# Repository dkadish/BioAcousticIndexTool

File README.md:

# BioAcoustic Index Tool (BAIT)

A smart, field-deployable sensor that automatically calculates acoustic indices and captures environmental data in real time.

BAIT records soundscape data and computes standard ecoacoustic metrics — including the **Acoustic Complexity Index (ACI)**, **Acoustic Diversity Index (ADI)**, and **Acoustic Difference Index (ADE)** — directly on-device. Environmental readings (temperature, humidity, light, and battery level) are logged alongside the acoustic data to SD card, with optional LoRaWAN transmission.

## Table of Contents

- [Project Overview](#project-overview)
- [Repository Structure](#repository-structure)
- [Hardware Versions](#hardware-versions)
- [Getting Started](#getting-started)
- [Contributing](#contributing)
- [License](#license)

## Project Overview

Traditional soundscape monitoring requires transporting recording equipment to the field, recording raw audio files, and then processing them offline. BAIT eliminates the offline processing step by computing acoustic indices on the microcontroller itself. This reduces storage requirements and allows near-real-time data delivery over low-power wide-area networks (LoRaWAN).

### Acoustic Indices Computed

| Index | Description |
|-------|-------------|
| **ACI** | Acoustic Complexity Index — captures the variability in sound intensity across frequency bins |
| **ADI** | Acoustic Diversity Index — measures the diversity of sound across frequency bands (Shannon entropy) |
| **ADE** | Acoustic Difference Index — measures the difference between consecutive time windows |
| **BI** | Bioacoustic Index — area of the mean spectrum above its minimum between 2 and 8 kHz |
| **H** | Total acoustic entropy — product of temporal (Ht) and spectral (Hf) entropy |
| **Events** | Acoustic event count — rises of the sound level above the background noise |

## Repository Structure

```
BioAcousticIndexTool/
├── firmware/
│   ├── bait/          # v1 firmware (Teensy 3.5 / 3.6 / MicroMod)
│   └── bait2/         # v2 firmware (Teensy MicroMod — active development)
├── electronics/
│   ├── BAIT.fzz       # v1 Fritzing schematic
│   └── BAIT2_MicroMod/ # v2 Eagle PCB & schematic
├── enclosure/
│   ├── BAIT.dwg       # AutoCAD drawing
│   └── BAIT.f3z       # Fusion 360 design
├── analysis/          # R & Python analysis notebooks
├── data/              # Sample raw and processed data
└── docs/              # Developer documentation
```

## Hardware Versions

### BAIT v1
- **Processor:** Teensy 3.5 or 3.6
- **PCB:** Custom carrier board designed in Fritzing
- **Sensors:** Si7021 (temperature/humidity), TSL2561 (light), battery voltage divider
- **Storage:** SD card via SdFat
- **Power:** Low-power sleep via Snooze library

### BAIT v2 (Active)
- **Processor:** Teensy MicroMod on SparkFun MicroMod carrier
- **PCB:** Custom Eagle carrier board ([`electronics/BAIT2_MicroMod`](electronics/BAIT2_MicroMod))
- **Sensors:** BME680 (temperature, humidity, pressure, gas), TSL2591 (light), BQ27441 LiPo fuel gauge
- **Communication:** LoRaWAN via Seeed WIO-E5 (The Things Network)
- **Storage:** SD card

## Getting Started

### Prerequisites

- [PlatformIO](https://platformio.org/) — used for building and uploading firmware
- [CLion](https://www.jetbrains.com/clion/) (recommended IDE) or VS Code with PlatformIO extension
- A Teensy MicroMod board (for BAIT v2) or Teensy 3.5/3.6 (for BAIT v1)

See [`docs/developing.md`](docs/developing.md) for detailed setup instructions.

### Building the Firmware

1. Clone this repository (including submodules):
   ```bash
   git clone --recurse-submodules https://github.com/dkadish/BioAcousticIndexTool.git
   ```

2. Open the relevant firmware directory in your IDE:
   - BAIT v2: `firmware/bait2/`
   - BAIT v1: `firmware/bait/`

3. Build and upload using PlatformIO:
   ```bash
   # For BAIT v2
   cd firmware/bait2
   pio run -e teensymm -t upload
   ```

   See each firmware directory's README for full build instructions.

### Data Analysis

The [`analysis/`](analysis/) directory contains Jupyter notebooks and R Markdown files for verifying acoustic index calculations and visualising results. See [`analysis/README.md`](analysis/README.md) for details.

## Contributing

Contributions are welcome! Please read [`docs/developing.md`](docs/developing.md) for information on setting up your development environment.

## License

This project is licensed under the terms in the [LICENSE](LICENSE) file.

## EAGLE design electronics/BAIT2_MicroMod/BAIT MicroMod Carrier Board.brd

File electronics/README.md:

# Electronics

Hardware design files for the BioAcoustic Index Tool (BAIT) custom carrier boards.

## Contents

| File / Directory | Description |
|-----------------|-------------|
| `BAIT.fzz` | BAIT v1 schematic and PCB layout (Fritzing) |
| `BAIT_bb.png` | BAIT v1 breadboard wiring diagram |
| `BAIT2_MicroMod/` | BAIT v2 custom carrier board for Teensy MicroMod (Eagle) |

## BAIT v1

The v1 board is a through-hole prototype carrier designed in [Fritzing](https://fritzing.org/).

**File:** `BAIT.fzz`

Open with the Fritzing application to view the schematic and breadboard layout.

## BAIT v2 — MicroMod Carrier Board (`BAIT2_MicroMod/`)

The v2 carrier board is designed in [Eagle](https://www.autodesk.com/products/eagle/overview) and mounts a **Teensy MicroMod** processor module.

| File | Description |
|------|-------------|
| `BAIT MicroMod Carrier Board.sch` | Eagle schematic |
| `BAIT MicroMod Carrier Board.brd` | Eagle PCB layout |
| `eagle.epf` | Eagle project file |
| `gerbers/` | Gerber files for PCB fabrication |
| `Assembly/` | Assembly documentation and BOM |

### Key Features

- **Processor socket:** SparkFun MicroMod M.2 connector (accepts Teensy MicroMod)
- **Sensors:** BME680 (temperature, humidity, pressure, gas), TSL2591 (light), BQ27441 (LiPo fuel gauge)
- **Communication:** Seeed WIO-E5 LoRaWAN module connector
- **Storage:** MicroSD card slot
- **Power:** LiPo battery connector with charging circuit

### Ordering PCBs

Use the Gerber files in `BAIT2_MicroMod/gerbers/` to order boards from a PCB fabrication service such as OSH Park, JLCPCB, or PCBWay.

## Tools Required

- [Fritzing](https://fritzing.org/) — for opening BAIT v1 design files
- [Autodesk Eagle](https://www.autodesk.com/products/eagle/overview) — for opening BAIT v2 design files

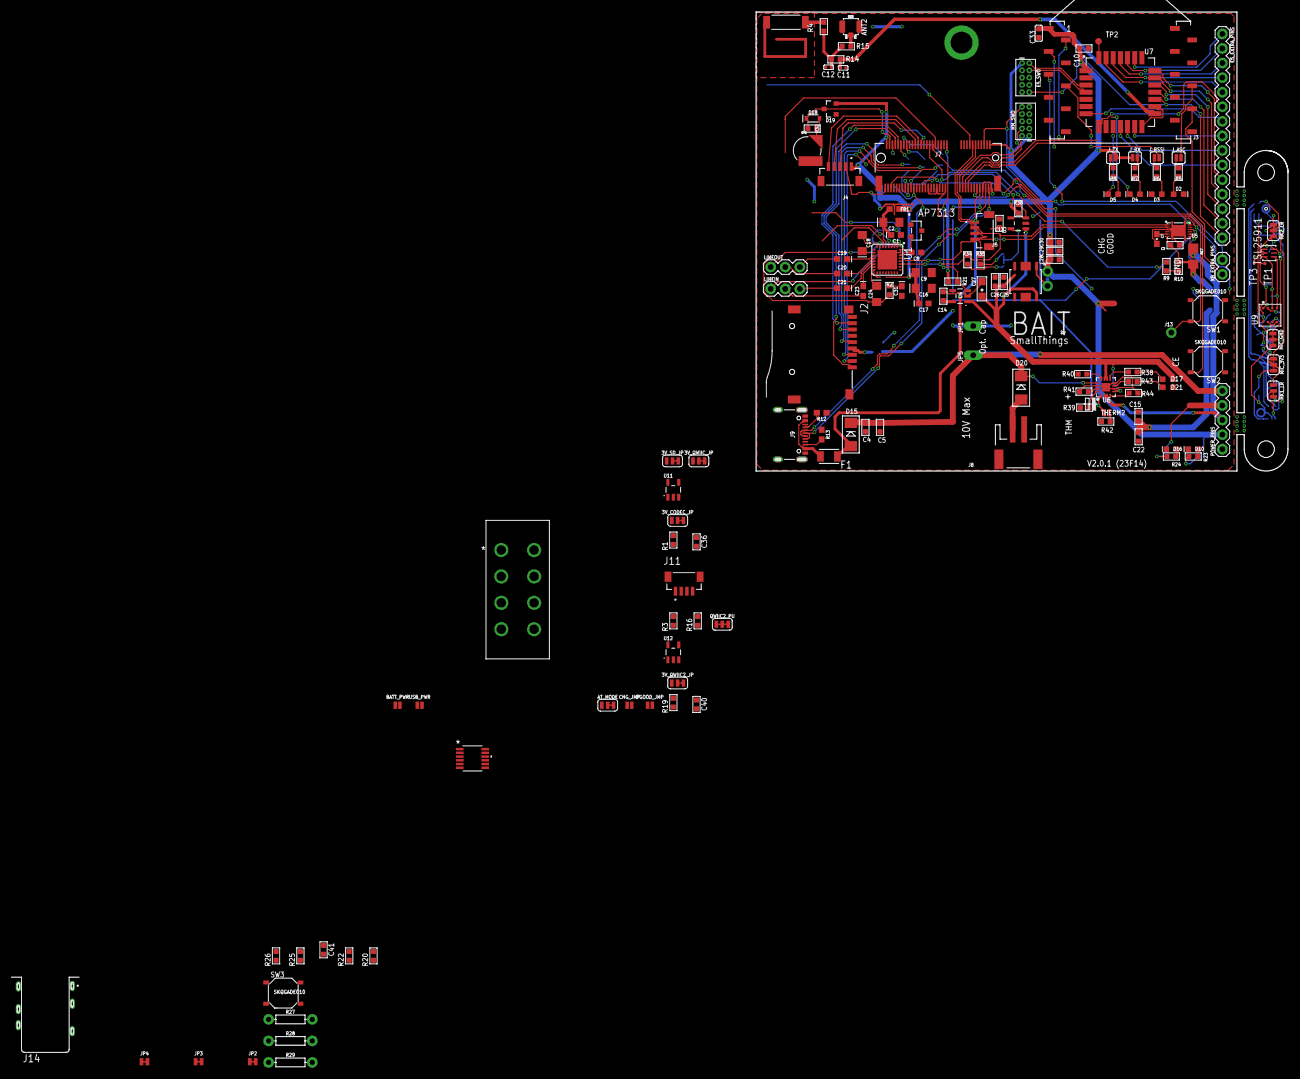
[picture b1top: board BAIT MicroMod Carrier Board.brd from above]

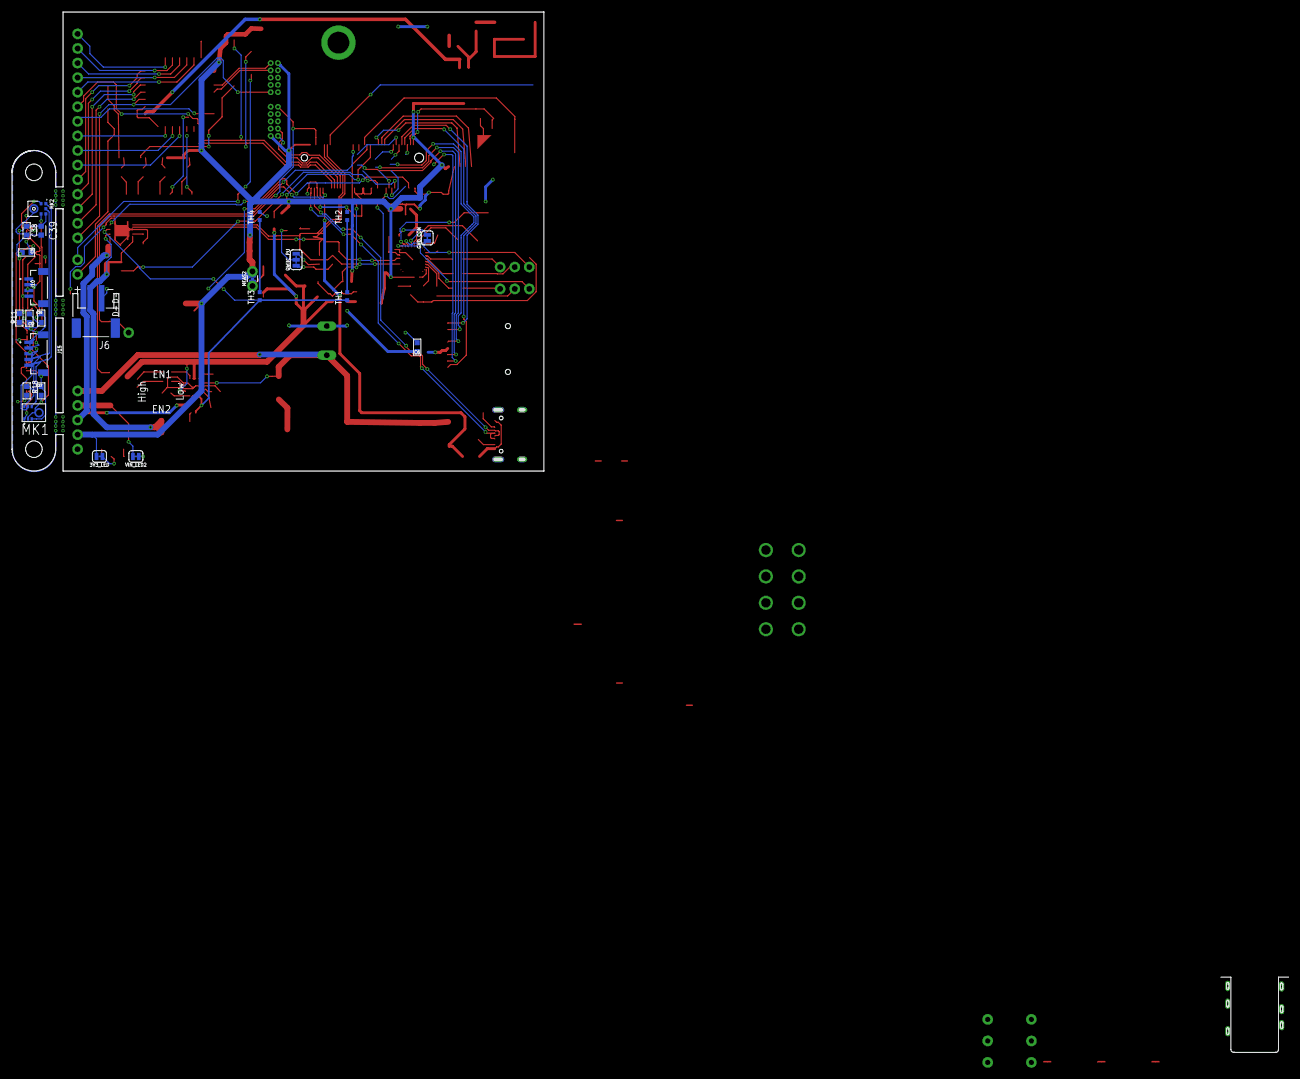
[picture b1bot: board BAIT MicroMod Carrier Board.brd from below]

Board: 2 copper layers, 92.7 x 80.0 mm, 174 parts (23 on the bottom side), 160 nets.

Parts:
3V3_LED: SMT-JUMPER_2_NC_TRACE_SILK
3V_CODEC_JP, 3V_QWIIC2_JP, 3V_QWIIC_JP, 3V_SD_JP: MK2_LR; SMT-JUMPER_3_1-NC_TRACE_SILK
ANT1: 0868AT43A0020EANT_0868AT43A0020E_JOT; ANT_0868AT43A0020E_JOT
ANT2: U-FL Connector; U-FL3P-SMD-2.6X2.6X1.0MM
AT_MODE: MK2_LR; SMT-JUMPER_3_1-NC_TRACE_SILK
BATT_PWR: SMT-JUMPER_2_NO_NO-SILK
BT1: ML414H; ML414H_IV01E
C1, C8, C17, C19, C20, C21, C23, C31: 2.2uF; 0603-POLAR
C2, C9, C16, C24: 0.1uF; EIA3216
C3, C13, C14, C28, C36, C40: 1uf; C0603
C4, C5, C10, C15, C22: 4.7uf; C0603
C6, C26, C29, C32, C34, C35, C37, C38, C41: 100nf; C0603
C7: 0.47uF; 0603-CAP
C11, C12: DNP; C0402
C18: 0.15uF; EIA3216
C25, C30: 220nf; C0603
C27: 10uf; AVX-A
C33: 4.7uF; C0603
C39: 220pF; CAPC1608X85
CHG_JMP: SMT-JUMPER_2_NO_NO-SILK
D2, D3, D4, D21: GREEN; LED-0603
D5, D10, D17: RED; LED-0603
D15, D20: SK34A; SMADIODE
D16: Yellow; LED-0603
D18: 3A/10V/280mV; SOD-323
D19: BAS70-05; SOT23-3
E5_EXTRA_PINS: 1X15
E5_SWO: JTAG; 2X5-PTH-1.27MM
F1: 6V/2A; FUSC3215X82N
FB1: 600Ω/1.8A; 0603
GND_CON: SMT-JUMPER_2_NC_TRACE_SILK
H5: STAND-OFF-REFLOW2.5MM_TALL; STAND-OFF-REFLOW-M2.5
J2: ST-TF-003A; SUNTECH_ST-TF-003A
J3: XBEE-SMD
J4, J15: BM05B-SRSS-TB(LF)(SN); JST_BM05B-SRSS-TB(LF)(SN)
J5, J10, J11: QWIIC_RIGHT_ANGLE; JST_BM04B-SRSS-TB(LF)(SN)
J6: JST 2PH; JST-PH-2-SMT-RA
J7: MICROMOD-2222-C; M.2-CONNECTOR-E
J8: JST-2-SMD
J9: USB-C-16P-2LAYER-PADS
J12: L203011MS02QECONN8_MS02QE_CNK; CONN8_MS02QE_CNK
J13: 1X01_NO_SILK
J14: SJ-3551B-MSMT-TR-67; CUI_SJ-3551B-MSMT-TR-67
JP1, JP5: 1X01_OVAL
JP2, JP3, JP4: JUMPER-SMT_2_NC_TRACE_NO-SILK; SMT-JUMPER_2_NC_TRACE_NO-SILK
J_ASC: JUMPER-SMT_2_NO_SILK; SMT-JUMPER_2_NO_SILK
J_RSSI: JUMPER-SMT_2_NO_SILK; SMT-JUMPER_2_NO_SILK
J_RX: JUMPER-SMT_2_NO_SILK; SMT-JUMPER_2_NO_SILK
J_TX: JUMPER-SMT_2_NO_SILK; SMT-JUMPER_2_NO_SILK
LINEIN: 1X03
LINEOUT: 1X03
MEAS2: COMBO-JUMPER_2_NC_TRACE
MIC_3V3: SMT-JUMPER_3_2-NC_TRACE_SILK
MIC_GND: SMT-JUMPER_3_2-NC_TRACE_SILK
MK1: ICS-43432
MK1_LR: MK1_LR; SMT-JUMPER_3_1-NC_TRACE_SILK
MK2: SPH0645LM4H-B; MIC_SPH0645LM4H-B
MK2_LR: MK2_LR; SMT-JUMPER_3_1-NC_TRACE_SILK
MM_SWO: JTAG; 2X5-PTH-1.27MM
PGOOD_JMP: SMT-JUMPER_2_NO_NO-SILK
POWER_PINS: 1X05
QWIIC2_PU: SMT-JUMPER_3_2-NC_TRACE_SILK
QWIIC_PU: SMT-JUMPER_3_2-NC_TRACE_SILK
R1, R18, R19, R20, R21, R36: 100K; R0603
R2, R3, R16, R34, R35: 2.2K; R0603
R4, R14, R15: 0R; R0603
R5, R11, R24: 4.7K; R0603
R6, R7, R8, R23, R40: 1K 1/10W; R0603
R9, R38, R41, R42, R43, R44: 10K 1/10W; R0603
R10: 20K; R0603
R12, R13: 5.1k; 0603
R17: 0.01; 1206
R22: 1.02M; R0603
R25: 61.9k; R0603
R26: 115k; R0603
R27, R28, R29: AXIAL-0.3
R32: 3.3K; R0603
R39: 590; R0603
SW1, SW2, SW3: SKQGADE010; SW4-SMD-5.2X5.2X1.5MM
TH1, TH2, TH3, TH4: 10k; THERM_NTCG163JX103DT1S
THERM2: SMT-JUMPER_2_NO_NO-SILK
TP1, TP3: PTR1TP06R; TP06R
TP2: TEST; TP-D45MIL
U1: SGTL5000-32; QFN-32-5MM
U2: AP7313; SOT-23_DIO
U3, U4, U11, U12: 3.3V; SOT23-5
U5: BQ27441-G1; PDSO-N12
U6: BQ24074; QFN16_3MM
U7: LoRa-E5-HF; MOUDLE28P-1.25-12X12X2.5MM
U8: S-1172B33-E6T1U; HSOP-6_FH006-A-P-SD-2.1_ABL
U9: BOSCH_TOOLS_BME680BOSCH_TOOLS_BME680_0_0; BOSCH_TOOLS_BME680_0
U10: TSL25911; SON-06-FN_2000X2400_AMS
U13: LTC2956IMS-1PBF; MSOP-12_MS_LIT
USB_PWR: SMT-JUMPER_2_NO_NO-SILK
VIN_LED2: SMT-JUMPER_2_NC_TRACE_SILK
XB_EXTRA_PINS: 1X02

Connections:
1.8V: C7.1, U5.5
3.3V: 3V3_LED.2, 3V_CODEC_JP.1, 3V_QWIIC2_JP.1, 3V_QWIIC_JP.1, 3V_SD_JP.1, AT_MODE.3, C10.2, C28.1, C29.1, C30.1, C33.2, D19.2, E5_SWO.1, J3.1, J4.1, J7.2, J7.74, J_RX.1, J_TX.2, MEAS2.2, MEAS2.4, MM_SWO.1, POWER_PINS.2, R1.2, R19.2, R21.2, R36.2, U7.1
3V3_B: C34.1, C35.1, J10.2, J15.1, MIC_3V3.2, MK1_LR.1, MK2_LR.3, TP1.TP, U9.8, U10.5
3V3_ICS: C37.1, MIC_3V3.3, MK1.3
3V3_SPH: C38.1, C39.1, MIC_3V3.1, MK2.5
3V_CODEC: 3V_CODEC_JP.3, C9.+, C16.+, C17.+, FB1.1, U1.20, U2.1
3V_EN: U8.3, U13.8
3V_QWIIC: 3V_QWIIC_JP.3, J5.2, QWIIC_PU.2
3V_QWIIC2: 3V_QWIIC2_JP.3, J11.2, QWIIC2_PU.2
3V_QWIIC_OUT: 3V_QWIIC_JP.2, C13.1
3V_QWIIC_OUT1: 3V_CODEC_JP.2, C36.1, U11.5
3V_QWIIC_OUT2: 3V_QWIIC2_JP.2, C40.1, U12.5
3V_SD: 3V_SD_JP.3, C6.1, J2.4
3V_SD_OUT: 3V_SD_JP.2, C14.1, U4.5
!BOOT!: J7.11, SW2.2
!CE: R44.1, U6.4
!CHG: R38.1, U6.9
!OFFALERT!: J7.38, U13.10
!ONALERT!: J7.34, U13.12
!PB: SW3.2, U13.7
!PBOUT!: J7.65, U13.9
!PGOOD: R43.1, U6.7
!RESET!: J7.6, J13.1, MM_SWO.10, SW1.2
!SLEEP!: J7.8, U13.11
AGND: C18.-, GND_CON.1, LINEIN.1, LINEOUT.1, U1.1, U1.3, U1.7
ASC: J3.15, J_ASC.2
CODEC_EN: J7.48, R1.1, U11.3
GND: ANT2.GND1, ANT2.GND2, AT_MODE.1, BT1.-, C1.-, C2.-, C3.2, C4.2, C5.2, C6.2, C7.2, C8.-, C9.-, C10.1, C11.1, C12.1, C13.2, C14.2, C15.2, C16.-, C17.-, C22.2, C25.2, C26.2, C27.-, C28.2, C29.2, C30.2, C31.-, C33.1, C36.2, C40.2, C41.2, D2.C, D3.C, D10.C, D16.C, E5_SWO.3, E5_SWO.5, E5_SWO.9, GND_CON.2, H5.1, J2.6, J2.G1, J2.G2, J2.G3, J2.G4, J3.10, J4.2, J5.1, J5.S1, J5.S2, J6.2, J7.1, J7.7, J7.33, J7.36, J7.39, J7.45, J7.75, J8.1, J9.GND, J9.GND2, J11.1, J11.S1, J11.S2, J14.6, JP1.1, MM_SWO.3, MM_SWO.5, MM_SWO.9, POWER_PINS.1, R9.1, R12.1, R13.1, R22.1, R25.1, R26.1, R27.P$1, R28.P$1, R29.P$1, R39.2, R40.2, R41.2, R42.2, R44.2, SW1.4, SW2.4, SW3.4, TH2.2, TH4.2, U1.31, U1.32, U1.PAD, U2.3, U3.2, U4.2, U5.3, U5.EP, U5.EP1, U5.EP2, U5.EP3, U5.EP4, U6.6, U6.8, U6.14, U6.THERMAL, U7.2, U7.14, U7.16, U7.22, U8.2, U8.5, U11.2, U12.2, U13.1, U13.6
GND_B: C32.2, C34.2, C35.2, J10.1, J10.S1, J10.S2, J15.2, J15.S1, J15.S2, MIC_GND.2, MK1_LR.3, MK2_LR.1, R18.1, TP3.TP, U9.1, U9.5, U9.7, U10.3
GND_ICS: C37.2, MIC_GND.3, MK1.2, MK1.4
GND_SPH: C38.2, C39.2, MIC_GND.1, MK2.3
GPOUT: J7.71, U5.12
HP_DETECT: J7.69, J14.5
I2C1_SCL: J7.53, J11.4, R16.1
I2C2_SDA: J11.3, R3.1
I2C_SCL: J5.4, J7.14, R35.1, U1.29, U5.2
I2C_SDA: J5.3, J7.12, R34.1, U1.27, U5.1
I2S2_MCLK: J7.63, U1.21
I2S2_RX: J7.18, U1.25
I2S2_SCK: J7.10, U1.24
I2S2_TX: J7.47, U1.26
I2S2_WS: J7.32, U1.23
I2S_SCK: J4.3, J7.50
I2S_SD: J4.4, J7.54
I2S_WS: J4.5, J7.52
ILIM: R40.1, U6.12
ISET: R39.1, U6.16
ITERM: R41.1, U6.15
unnamed: QWIIC2_PU.3, R16.2
unnamed: QWIIC2_PU.1, R3.2
unnamed: J_RX.2, R7.2
unnamed: J9.A5, R12.2
unnamed: J9.B5, R13.2
unnamed: MEAS2.1, MEAS2.3, U8.1
unnamed: ANT2.D, R15.2
unnamed: J14.2, U1.6
unnamed: D4.A, R7.1
unnamed: R42.1, THERM2.1
unnamed: ANT1.1, R4.2
unnamed: C19.-, LINEOUT.3
unnamed: C20.-, LINEOUT.2
unnamed: C21.-, LINEIN.3
unnamed: 3V3_LED.1, R23.2
unnamed: C23.-, LINEIN.2
unnamed: C19.+, U1.11
unnamed: TP2.T, U7.28
unnamed: C20.+, U1.12
unnamed: C21.+, U1.13
unnamed: C23.+, U1.14
unnamed: BT1.+, D18.A, R32.1
unnamed: QWIIC_PU.3, R35.2
unnamed: J_ASC.1, R5.2
unnamed: QWIIC_PU.1, R34.2
unnamed: D10.A, R23.1
unnamed: C12.2, R4.1, R14.2, R15.1
unnamed: R24.2, VIN_LED2.1
unnamed: D20.A, J8.2
unnamed: D17.C, R38.2
unnamed: D21.C, R43.2
unnamed: C24.-, J14.1, R2.2
unnamed: D2.A, R5.1
unnamed: J14.3, U1.2
unnamed: F1.1, J9.VBUS1, J9.VBUS2
unnamed: D16.A, R24.1
unnamed: C18.+, U1.10
unnamed: C24.+, U1.15
unnamed: C8.+, U1.30, U2.2
unnamed: J_RSSI.1, R6.2
unnamed: D3.A, R6.1
unnamed: J_TX.1, R8.2
unnamed: D5.A, R8.1
unnamed: C1.+, C2.+, FB1.2, U1.5
unnamed: J14.4, U1.4
unnamed: TH3.2, TH4.1
unnamed: TH1.2, TH2.1
unnamed: C32.1, R11.2, U9.6
unnamed: R11.1, U9.2
unnamed: D21.A, PGOOD_JMP.1
unnamed: CHG_JMP.1, D17.A
unnamed: JP3.2, R20.2, R28.P$2, U13.3
unnamed: JP2.1, R22.2
unnamed: JP4.2, R29.P$2, U13.4
unnamed: JP2.2, R20.1, R27.P$2, U13.2
unnamed: JP3.1, R25.2
unnamed: JP4.1, R26.2
unnamed: C31.+, R2.1, U1.16
PA0/D0: E5_EXTRA_PINS.1, U7.23
PA2/TX2: E5_EXTRA_PINS.13, U7.19
PA3/RX2: E5_EXTRA_PINS.14, U7.18
PA9/D9: E5_EXTRA_PINS.11, U7.21
PA10/MOSI: E5_EXTRA_PINS.5, U7.27
PA13/SWDIO: E5_SWO.2, U7.3
PA14/SWCLK: E5_SWO.4, U7.4
PB3/A3: E5_EXTRA_PINS.6, U7.8
PB4/A4: E5_EXTRA_PINS.7, U7.7
PB5/LED: E5_EXTRA_PINS.10, U7.11
PB9/NSS: E5_EXTRA_PINS.3, U7.25
PB10/D10: E5_EXTRA_PINS.12, U7.20
PB13/BOOT/SCK: AT_MODE.2, E5_EXTRA_PINS.2, U7.24
PB14/MISO: E5_EXTRA_PINS.4, U7.26
PC0/RX1: E5_EXTRA_PINS.8, U7.13
PC1/TX1: E5_EXTRA_PINS.9, U7.12
QWIIC2_EN: J7.46, R19.1, U12.3
QWIIC_EN: J7.44, R36.1, U3.3
RF: C11.2, R14.1, U7.15
RSSI: J3.6, J_RSSI.2
RST: E5_EXTRA_PINS.15, E5_SWO.10, U7.17
RTC_3V: D18.C, D19.3, J7.72, R32.2
RX: D4.C, J3.2, J7.19, U7.10
SCK_B: J15.3, MK1.6, MK2.4
SCL_B: J10.4, U9.4, U10.1
SDA_B: J10.3, U9.3, U10.6
SD_B: J15.4, MK1.7, MK2.6, R18.2
SD_CLK: J2.5, J7.60
SD_CMD: J2.3, J7.62
SD_DATA0: J2.7, J7.64
SD_DATA1: J2.8, J7.66
SD_DATA2: J2.1, J7.68
SD_DATA3: J2.2, J7.70
SD_DETECT: J2.9, J7.73
SD_EN: J7.42, R21.1, U4.3
SEL_MK1: MK1.1, MK1_LR.2
SEL_MK2: MK2.2, MK2_LR.2
SWDCK: J7.21, MM_SWO.4
SWDIO: J7.23, MM_SWO.2
TS: TH1.1, TH3.1, THERM2.2, U5.10, U6.1
TX: D5.C, J3.3, J7.17, U7.9
USB_D+: J7.3, J9.A6, J9.B6
USB_D-: J7.5, J9.A7, J9.B7
USB_VIN: D15.A, F1.2, J7.9
V+: C25.1, C26.1, C27.+, C41.1, CHG_JMP.2, PGOOD_JMP.2, POWER_PINS.4, U3.1, U4.1, U6.5, U6.10, U6.11, U8.6, U11.1, U12.1, U13.5, VIN_LED2.2
VBUS: C4.1, C5.1, D20.C, J12.1, J12.3, JP5.1, POWER_PINS.5, U6.13, USB_PWR.1
VIN: BATT_PWR.1, C3.1, C15.1, C22.1, J12.5, J12.7, R10.2, R17.2, U5.6, U5.8
VIN/3: J7.49, R9.2, R10.1
V_BATT: POWER_PINS.3, R17.1, U5.7, U6.2, U6.3
V_BATT_IN: BATT_PWR.2, J6.1, J12.6
V_USB_IN: D15.C, J12.2, USB_PWR.2
WS_B: J15.5, MK1.5, MK2.1
XB_ON: J3.13, XB_EXTRA_PINS.1
XB_RST: J3.5, XB_EXTRA_PINS.2

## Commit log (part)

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2021-01-14 Git ignore file
2021-01-15 Firmware ignore
2021-01-15 updated ignore
2021-01-15 Firmware first commit
2021-01-15 Raw and processed sensor data
2021-01-15 iPython notebook used to analyze data for the paper
2021-01-15 Electronics as a fritizing file
2021-01-15 Enclosure archive files
2021-04-16 Implements testing routines, fixes FFT averaging, adds modified ACI
    This commit does 3 major things:
    1. Implements testing routines. Implements 3 files (test_*.cpp) that test the ACI algorithm on a set of WAV files saved to an SD card for comparison with the soundecology R package.
    2. Fixes FFT averaging. The Teensy Audio Library by default returns FFT results as the average of 8 FFT readings. This does not work well for ACI, so this commit adds an option to set the averaging a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
    3. Implements modified ACI. Implements the ACI algorithm modification from Farina et. al. 2016. Adds new options to ACI_TemporalWindow constructor.
2021-04-16 Created using Colaboratory
2021-04-19 ACI Verification code and data
2022-07-29 HW ideas
2022-07-29 Eagle files commit
2022-07-29 Schematic V1 complete
2022-08-01 Initial board layout
2022-08-05 Board layout updates
2023-05-23 Updates to work with the latest clion and pio
2023-05-23 Added docs
2023-05-23 Ignore update
2023-05-23 Updated ignores
2023-05-23 Compiling for MM
2023-05-23 Rename SBAT to BAIT
2023-05-23 Formatting updates
2023-05-29 A couple of working local libraries and a new structure for the project.
2023-05-31 Added some statuses and display
2023-07-29 Some updates to try to get sdio working
2023-07-29 Files for First Prototype production
2023-07-30 Schematic fix for faulty connection between Teensy and LORA-E5
    Swapped RX and TX pins. Fixes #7
2023-07-30 Connect SGTL to I2S2 pins on micromod connector
    Solves #6 in schematic, but creates #14
2023-07-30 Fixes enable issue with main 3.3V regulator
    Resolves #3 in schematic and board
2023-08-02 Removes secondary options for connecting to SD card
    Resolves #22
2023-08-02 Removes testing buzzer
    Resolves #21 and partially #14
2023-08-02 Updated the JST connectors
    Switched to the correct (vertical orientation) connector and swapped the 6-pin audio connector for a 5-pin version
2023-08-02 Also removed LR_SEL from MicroMod schematic
2023-08-03 Added 3V3 regulators and options to power direct from 3V3 line
    Added a regulator for the SGTL5000 and renamed lines from the SD and qwiic regulators. Added enable lines and jumpers to bypass the regulators if necessary.
2023-08-03 Added second Qwiic port, connected to I2C2 (teensy)
    Also added power control for this qwiic
2023-08-07 Adds assembly variants that remove RSSI LEDs
    Resolves #27
2023-08-07 Connected SD card detect pin to micromod
    Resolves #25
2023-08-07 Connect headphone switches to teensy ports
    Resolves #24
2023-08-15 Library Update
2023-08-15 Updates pin 24 connection on WIO
    Solves #8
2023-09-05 Not sure what these changes are, but committing for posterity
2023-09-05 Fixed Cayenne Dependency
2023-09-08 Some updates to the setup
2023-09-10 Updated private library organisation
2023-09-13 Auto stash before merge of "feature/indices" and "origin/feature/v2_firmware"
2023-09-13 Version with acoustic indices from BAIT1 that compiles
2023-09-18 Updated layout for TC2956 chip
    Should resolve #29, but I should double check
2023-09-20 Fixed headphone jack detection
2024-04-19 Testing test file
2024-06-25 Working sd card and battery sensor
    Though the battery sensor's values are strange...
2024-06-25 Added debugging timers, USB audio mode, working FFT recording
2024-06-25 Don't record raw ffts
2024-06-25 gitflow-feature-stash: ecoacoustics_rms
2024-06-25 ignore autogenerated file
2024-06-26 RMS seems to work!
2024-06-27 Updates the RMS print message
2024-06-28 Working battery status messages
2024-06-30 Implements a 1 second send delay so that all data from the same time frame from different sensors gets sent together
2024-06-30 Working BME680 sensor
2024-07-01 Working light sensor using a modified version of the Adafruit TSL2591 library
2024-07-01 ACI seems to be working. Should be tested
2024-07-01 Updated light parameters
2024-07-01 Changed interval to 120 ms, partially working again
    Still getting a NaN for the final calculation, which is odd. Not all the time, but sometimes.
2024-07-06 Added the big battery
2024-10-23 Updates microphone gains
2025-03-04 Working send via LoRa, but sending 2x messages
2025-03-10 Multiply RMS by 100 to adjust range
    Perhaps this just means that the mic volume is too low. Need to test in field.
2025-03-10 Put raw light values behind a define
    They don't give any useful data.
2025-03-16 Getting ACI working
2025-03-16 Fixes an error in the ACI calculation where it was not resetting
2025-03-16 Fixes power sensor not reporting
2025-03-21 First try at TVSP
2026-02-23 Configure README specialist agent with capabilities
    Updated agent configuration to specify its focus on README files and project documentation. Added detailed capabilities and limitations for the agent.
2026-02-23 Rename my-agent.agent.md to readme-specialist.agent.md
2026-02-23 Initial plan
2026-02-23 docs: improve root README and add README files for all subcomponents
2026-02-23 Add PlatformIO Code Documentation Agent README
2026-02-23 Add platformio-documentation-specialist agent metadata
    Added metadata for platformio-documentation-specialist agent.
2026-02-23 docs: expand docs/developing.md from stub into comprehensive development guide
2026-02-23 test: verify commit mechanism works before creating docs structure
2026-02-23 docs: add comprehensive API and usage documentation for firmware/bait2
2026-02-23 docs: add Doxyfile to generate HTML API docs into firmware/bait2/docs/
2026-02-23 docs: configure Doxygen to output HTML directly to firmware/bait2/docs/
2026-03-02 build fixes

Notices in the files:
parts and their libraries:
SparkFun-Jumpers: Licensing: Creative Commons ShareAlike 4.0 International - https://creativecommons.org/licenses/by-sa/4.0
COPYRIGHT: Copyright (C) 2022 Ultra Librarian. All rights reserved.
COPYRIGHT: Copyright (C) 2023 Ultra Librarian. All rights reserved.
